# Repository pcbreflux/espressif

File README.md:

# espressif
espressif stuff (i.e. ESP32, ESP8266)

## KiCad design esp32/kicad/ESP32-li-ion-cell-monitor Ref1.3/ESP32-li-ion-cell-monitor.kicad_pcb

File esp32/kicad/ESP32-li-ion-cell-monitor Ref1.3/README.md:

# ESP32 Li-Ion Cell Monitor (:battery: i.e. 18650 ...  :zap:)
===========================

## Application: kicad

## Version: 5.0.0-fee4fd1~66~ubuntu18.04.1, release build

## Libraries:

    wxWidgets 3.0.4

    libcurl/7.58.0 OpenSSL/1.1.0g zlib/1.2.11 libidn2/2.0.4 libpsl/0.19.1 (+libidn2/2.0.4) nghttp2/1.30.0 librtmp/2.3

## Platform: Linux 4.15.0-29-generic x86_64, 64 bit, Little endian, wxGTK

## Build Info:

    wxWidgets: 3.0.4 (wchar_t,wx containers,compatible with 2.8) GTK+ 2.24

    Boost: 1.65.1

    OpenCASCADE Community Edition: 6.9.1

    Curl: 7.58.0

    Compiler: GCC 7.3.0 with C++ ABI 1011

## Build settings:

    USE_WX_GRAPHICS_CONTEXT=OFF

    USE_WX_OVERLAY=OFF

    KICAD_SCRIPTING=ON

    KICAD_SCRIPTING_MODULES=ON

    KICAD_SCRIPTING_WXPYTHON=OFF

    KICAD_SCRIPTING_ACTION_MENU=ON

    BUILD_GITHUB_PLUGIN=ON

    KICAD_USE_OCE=ON

    KICAD_USE_OCC=OFF

    KICAD_SPICE=ON

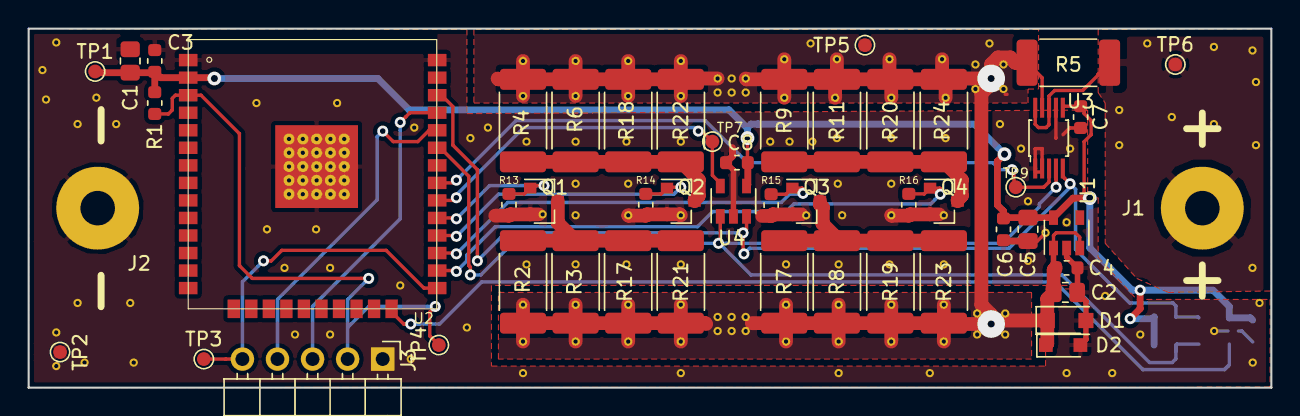
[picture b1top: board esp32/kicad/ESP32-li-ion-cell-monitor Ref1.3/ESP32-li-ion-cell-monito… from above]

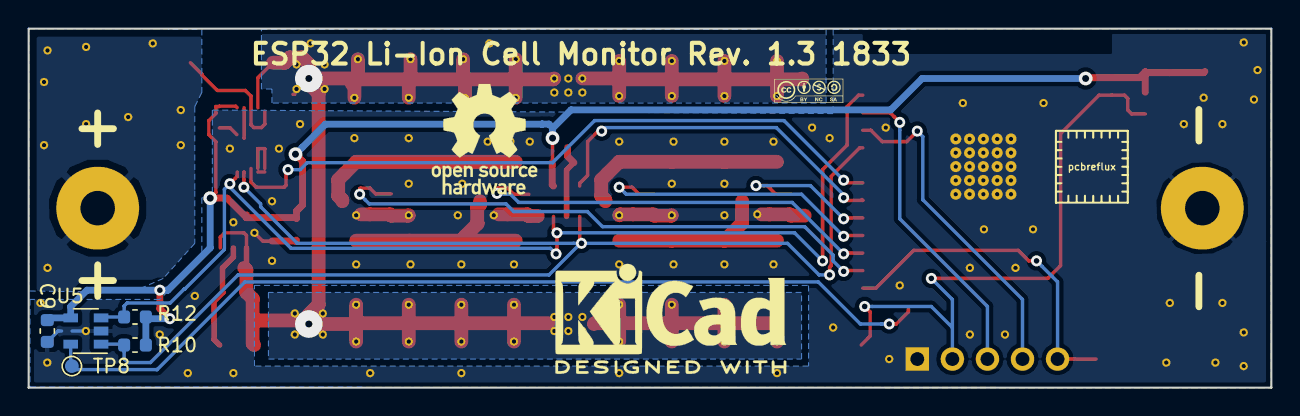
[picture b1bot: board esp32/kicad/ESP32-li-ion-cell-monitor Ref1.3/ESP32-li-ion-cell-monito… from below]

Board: 2 copper layers, 90.0 x 26.0 mm, 56 parts (5 on the bottom side), 21 nets.

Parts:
C1: 1u; C_0805_2012Metric
C2, C5: 10u; C_0805_2012Metric
C3, C4, C6, C7, C8, C9: 100n; C_0603_1608Metric
D1: MMSZ5V6CF; D_SOD-123F
D2: ESDZL5-1F4; D_SOD-323_HandSoldering
J1, J2: Conn_01x01_Female; SolderWirePad_1x01_Drill2.5mm
J3: Conn_01x05_Male; PinHeader_1x05_P2.54mm_Horizontal
Q1, Q2, Q3, Q4: Q_NMOS_GSD; SOT-23
R1, R10, R12: 10k; R_0603_1608Metric
R2, R3, R4, R6, R7, R8, R9, R11, R17, R18, R19, R20, R21, R22, R23, R24: 100R; R_2512_6332Metric_Pad1.52x3.35mm_HandSolder
R5: 100mR; R_2512_6332Metric_Pad1.52x3.35mm_HandSolder
R13, R14, R15, R16: 100k; R_0603_1608Metric
TP1, TP2, TP3, TP4, TP5, TP6, TP7, TP8, TP9: Test_Point; TestPoint_Pad_D1.0mm
U1: XC6220B281MR-G; SOT-23-5
U2: ESP-WROOM-32; ESP-WROOM-32-short
U3: INA226_SOT25-5; VSSOP-10_3.1x3.1mm_P0.5mm
U4: Si7060-00; SOT-23-5
U5: Si7060-01; SOT-23-5

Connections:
+2V8: C1.2, C3.2, C5.1, C6.1, C7.1, C8.2, C9.2, R1.2, R10.2, R12.2, TP1.1, U1.5, U2.2, U3.6, U4.4, U5.4
+BATT: J1.1, R5.2, TP6.1, U3.8, U3.10
/Alert1: TP9.1, U2.31, U3.3
/Alert2: TP7.1, U2.30, U4.5
/Alert3: TP8.1, U2.24, U5.5
/BOOT: J3.5, TP3.1, U2.25
/EN: J3.2, R1.1, TP4.1, U2.3
/RX: J3.4, U2.34
/SCL: R12.1, U2.36, U3.5, U4.3, U5.3
/SDA: R10.1, U2.33, U3.4, U4.1, U5.1
/TX: J3.3, U2.35
GND: C1.1, C2.2, C3.1, C4.2, C5.2, C6.2, C7.2, C8.1, C9.1, D1.2, D2.2, J2.1, J3.1, Q1.2, Q2.2, Q3.2, Q4.2, R13.1, R14.1, R15.1, R16.1, TP2.1, U1.2, U2.1, U2.38, U2.39, U3.1, U3.2, U3.7, U4.2, U5.2
unnamed: Q1.1, R13.2, U2.29
unnamed: Q1.3, R2.2, R3.2, R17.2, R21.2
unnamed: Q2.1, R14.2, U2.28
unnamed: Q2.3, R4.2, R6.2, R18.2, R22.2
unnamed: Q3.1, R15.2, U2.27
unnamed: Q3.3, R7.2, R8.2, R19.2, R23.2
unnamed: Q4.1, R16.2, U2.26
unnamed: Q4.3, R9.2, R11.2, R20.2, R24.2
VCC: C2.1, C4.1, D1.1, D2.1, R2.1, R3.1, R4.1, R5.1, R6.1, R7.1, R8.1, R9.1, R11.1, R17.1, R18.1, R19.1, R20.1, R21.1, R22.1, R23.1, R24.1, TP5.1, U1.1, U1.3, U3.9

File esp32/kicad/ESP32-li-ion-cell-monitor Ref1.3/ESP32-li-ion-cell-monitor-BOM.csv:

"Id";"Designator";"Package";"Quantity";"Designation";"Supplier and ref";
1;"REF**,REF**,REF**,REF**,REF**,REF**,REF**,REF**,REF**,REF**,REF**,REF**,REF**,REF**,REF**,REF**,REF**,REF**,REF**,REF**,REF**,REF**,REF**,REF**,REF**,REF**,REF**,REF**,REF**,REF**,REF**,REF**,REF**,REF**,REF**,REF**,REF**,REF**,REF**,REF**,REF**,REF**,REF**,REF**,REF**,REF**,REF**,REF**,REF**,REF**,REF**,REF**,REF**,REF**,REF**,REF**,REF**,REF**,REF**,REF**,REF**,REF**,REF**,REF**,REF**,REF**,REF**,REF**,REF**,REF**,REF**,REF**,REF**,REF**,REF**,REF**,REF**,REF**,REF**,REF**,REF**,REF**,REF**,REF**,REF**,REF**,REF**,REF**,REF**,REF**,REF**,REF**,REF**,REF**,REF**,REF**,REF**,REF**,REF**,REF**,REF**,REF**,REF**,REF**,REF**,REF**,REF**,REF**,REF**,REF**,REF**,REF**,REF**,REF**,REF**,REF**,REF**,REF**,REF**,REF**,REF**,REF**,REF**,REF**,REF**,REF**,REF**,REF**,REF**,REF**,REF**,REF**,REF**,REF**,REF**,REF**,REF**,REF**";"Via-0.6mm";138;"Via-0.6mm";;;
2;"TP9,TP1,TP2,TP3,TP4,TP5,TP6,TP7,TP8";"TestPoint_Pad_D1.0mm";9;"Test_Point";;;
3;"J3";"PinHeader_1x05_P2.54mm_Horizontal";1;"Conn_01x05_Male";;;
4;"U2";"ESP-WROOM-32-short";1;"ESP-WROOM-32";;;
5;"U4";"SOT-23-5";1;"Si7060-00";;;
6;"C1";"C_0805_2012Metric";1;"1u";;;
7;"C4,C6,C3,C7,C8,C9";"C_0603_1608Metric";6;"100n";;;
8;"C5,C2";"C_0805_2012Metric";2;"10u";;;
9;"Q1,Q2,Q3,Q4";"SOT-23";4;"Q_NMOS_GSD";;;
10;"R1,R10,R12";"R_0603_1608Metric";3;"10k";;;
11;"U5";"SOT-23-5";1;"Si7060-01";;;
12;"REF**";"pcbreflux_logo";1;"pcbreflux_logo";;;
13;"REF**";"OSHW-Logo_7.5x8mm_SilkScreen";1;"OSHW-Logo_7.5x8mm_SilkScreen";;;
14;"REF**";"KiCad-Logo2_8mm_SilkScreen";1;"KiCad-Logo2_8mm_SilkScreen";;;
15;"G***";"Logo_silk_CC-BY-NC-SA_5x2mm";1;"LOGO";;;
16;"D1";"D_SOD-123F";1;"MMSZ5V6CF";;;
17;"D2";"D_SOD-323_HandSoldering";1;"ESDZL5-1F4";;;
18;"R2,R3,R4,R6,R7,R8,R9,R11,R17,R18,R19,R20,R21,R22,R23,R24";"R_2512_6332Metric_Pad1.52x3.35mm_HandSolder";16;"100R";;;
19;"R5";"R_2512_6332Metric_Pad1.52x3.35mm_HandSolder";1;"100mR";;;
20;"U1";"SOT-23-5";1;"XC6220B281MR-G";;;
21;"U3";"VSSOP-10_3.1x3.1mm_P0.5mm";1;"INA226_SOT25-5";;;
22;"R13,R14,R15,R16";"R_0603_1608Metric";4;"100k";;;
23;"J1,J2";"SolderWirePad_1x01_Drill2.5mm";2;"Conn_01x01_Female";;;

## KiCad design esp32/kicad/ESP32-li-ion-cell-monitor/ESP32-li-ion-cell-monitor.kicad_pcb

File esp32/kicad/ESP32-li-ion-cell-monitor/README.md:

# ESP32 Li-Ion Cell Monitor (:battery: i.e. 18650 ...  :zap:)
===========================

## Application: kicad

## Version: 6.0.0-rc1-unknown-7dfc4e3~65~ubuntu18.04.1, release build

## Libraries:

    wxWidgets 3.0.4

    libcurl/7.58.0 OpenSSL/1.1.0g zlib/1.2.11 libidn2/2.0.4 libpsl/0.19.1 (+libidn2/2.0.4) nghttp2/1.30.0 librtmp/2.3

## Platform: Linux 4.15.0-29-generic x86_64, 64 bit, Little endian, wxGTK

## Build Info:

    wxWidgets: 3.0.4 (wchar_t,wx containers,compatible with 2.8) GTK+ 2.24

    Boost: 1.65.1

    OpenCASCADE Community Edition: 6.9.1

    Curl: 7.58.0

    Compiler: GCC 7.3.0 with C++ ABI 1011

## Build settings:

    USE_WX_GRAPHICS_CONTEXT=OFF

    USE_WX_OVERLAY=OFF

    KICAD_SCRIPTING=ON

    KICAD_SCRIPTING_MODULES=ON

    KICAD_SCRIPTING_WXPYTHON=OFF

    KICAD_SCRIPTING_ACTION_MENU=ON

    BUILD_GITHUB_PLUGIN=ON

    KICAD_USE_OCE=ON

    KICAD_USE_OCC=OFF

    KICAD_SPICE=ON

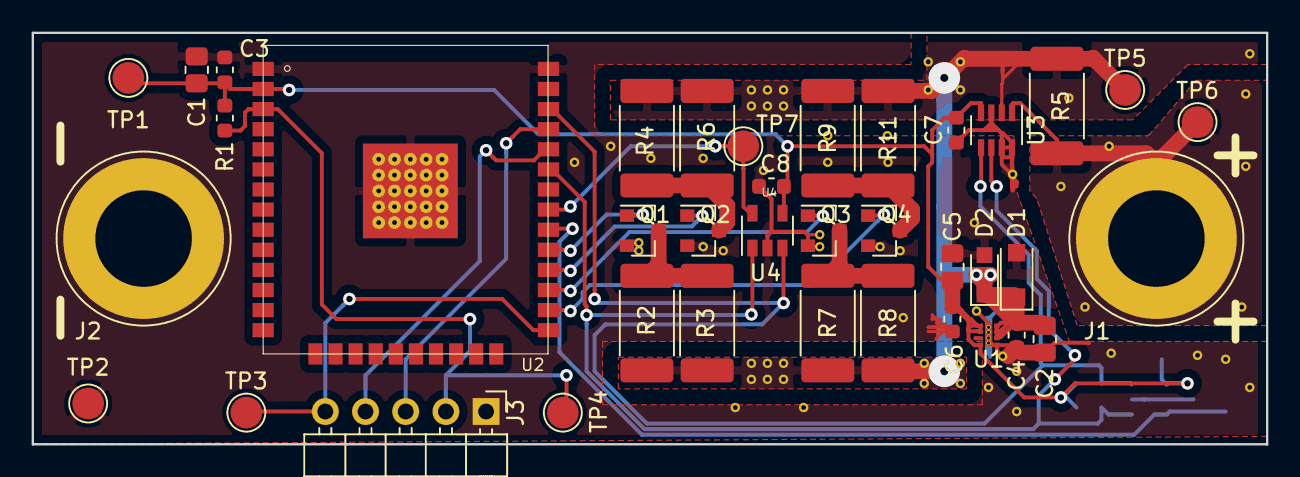
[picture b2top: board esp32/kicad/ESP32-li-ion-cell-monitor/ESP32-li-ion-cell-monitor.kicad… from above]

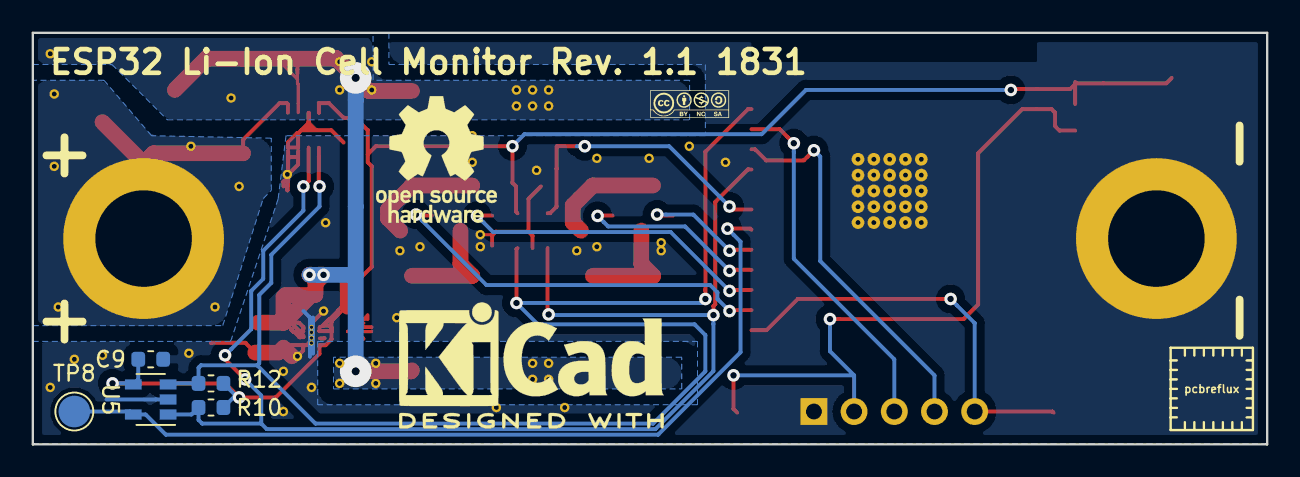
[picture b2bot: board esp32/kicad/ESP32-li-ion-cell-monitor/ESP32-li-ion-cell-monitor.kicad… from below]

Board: 2 copper layers, 78.0 x 26.0 mm, 43 parts (5 on the bottom side), 20 nets.

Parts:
C1, C2, C5: 1u; C_0805_2012Metric
C3, C4, C6, C7, C8, C9: 100n; C_0603_1608Metric
D1: MMSZ5V6CF; D_SOD-123F
D2: ESDZL5-1F4; D_SOD-323_HandSoldering
J1, J2: Conn_01x01_Female; Banana_Jack_1Pin
J3: Conn_01x05_Male; PinHeader_1x05_P2.54mm_Horizontal
Q1, Q2, Q3, Q4: Q_NMOS_GSD; SOT-23
R1, R10, R12: 10k; R_0603_1608Metric
R2, R3, R4, R6, R7, R8, R9, R11: 10R; R_2512_6332Metric_Pad1.52x3.35mm_HandSolder
R5: 100mR; R_2512_6332Metric_Pad1.52x3.35mm_HandSolder
TP1, TP2, TP3, TP4, TP5, TP6, TP7, TP8: Test_Point; TestPoint_Pad_D2.0mm
U1: NCP186B; XDFN8
U2: ES-WROOM-32; ESP-WROOM-32-short
U3: INA219_SOT23-8; SOT-23-8
U4: Si7060-00; SOT-23-5
U5: Si7060-01; SOT-23-5

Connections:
+3V: C1.2, C3.2, C5.1, C6.1, C7.2, C8.2, C9.2, R1.2, R10.2, R12.2, TP1.1, U1.1, U1.2, U1.4, U2.2, U3.4, U4.4, U5.4
+BATT: J1.1, R5.2, TP6.1, U3.1
/Alert1: TP7.1, U2.31, U4.5
/Alert2: TP8.1, U2.30, U5.5
/BOOT: J3.5, TP3.1, U2.25
/EN: J3.2, R1.1, TP4.1, U2.3
/RX: J3.4, U2.34
/SCL: R12.1, U2.36, U3.5, U4.3, U5.3
/SDA: R10.1, U2.33, U3.6, U4.1, U5.1
/TX: J3.3, U2.35
GND: C1.1, C2.2, C3.1, C4.2, C5.2, C6.2, C7.1, C8.1, C9.1, D1.2, D2.2, J2.1, J3.1, Q1.2, Q2.2, Q3.2, Q4.2, TP2.1, U1.5, U1.9, U2.1, U2.38, U2.39, U3.3, U3.7, U3.8, U4.2, U5.2
unnamed: Q1.1, U2.29
unnamed: Q1.3, R2.2, R3.2
unnamed: Q2.1, U2.28
unnamed: Q2.3, R4.2, R6.2
unnamed: Q3.1, U2.27
unnamed: Q3.3, R7.2, R8.2
unnamed: Q4.1, U2.26
unnamed: Q4.3, R9.2, R11.2
VCC: C2.1, C4.1, D1.1, D2.1, R2.1, R3.1, R4.1, R5.1, R6.1, R7.1, R8.1, R9.1, R11.1, TP5.1, U1.6, U1.7, U1.8, U3.2

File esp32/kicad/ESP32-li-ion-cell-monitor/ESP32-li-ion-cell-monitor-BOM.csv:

"Id";"Designator";"Package";"Quantity";"Designation";"Supplier and ref";
1;"U1";"XDFN8";1;"NCP186B";;;
2;"U3";"SOT-23-8";1;"INA219_SOT23-8";;;
3;"REF**,REF**,REF**,REF**,REF**,REF**,REF**,REF**,REF**,REF**,REF**,REF**,REF**,REF**,REF**,REF**,REF**,REF**,REF**,REF**,REF**,REF**,REF**,REF**,REF**,REF**,REF**,REF**,REF**,REF**,REF**,REF**,REF**,REF**,REF**,REF**,REF**,REF**,REF**,REF**,REF**,REF**,REF**,REF**,REF**,REF**,REF**,REF**,REF**,REF**,REF**,REF**,REF**,REF**,REF**,REF**,REF**,REF**";"Via-0.6mm";58;"Via-0.6mm";;;
4;"J3";"PinHeader_1x05_P2.54mm_Horizontal";1;"Conn_01x05_Male";;;
5;"U2";"ESP-WROOM-32-short";1;"ES-WROOM-32";;;
6;"U4";"SOT-23-5";1;"Si7060-00";;;
7;"C1,C5,C2";"C_0805_2012Metric";3;"1u";;;
8;"C4,C6,C3,C7,C8,C9";"C_0603_1608Metric";6;"100n";;;
9;"Q1,Q2,Q3,Q4";"SOT-23";4;"Q_NMOS_GSD";;;
10;"TP1,TP2,TP3,TP4,TP5,TP6,TP7,TP8";"TestPoint_Pad_D2.0mm";8;"Test_Point";;;
11;"R1,R10,R12";"R_0603_1608Metric";3;"10k";;;
12;"U5";"SOT-23-5";1;"Si7060-01";;;
13;"REF**";"pcbreflux_logo";1;"pcbreflux_logo";;;
14;"REF**";"OSHW-Logo_7.5x8mm_SilkScreen";1;"OSHW-Logo_7.5x8mm_SilkScreen";;;
15;"REF**";"KiCad-Logo2_8mm_SilkScreen";1;"KiCad-Logo2_8mm_SilkScreen";;;
16;"G***";"Logo_silk_CC-BY-NC-SA_5x2mm";1;"LOGO";;;
17;"D1";"D_SOD-123F";1;"MMSZ5V6CF";;;
18;"D2";"D_SOD-323_HandSoldering";1;"ESDZL5-1F4";;;
19;"R2,R3,R4,R6,R7,R8,R9,R11";"R_2512_6332Metric_Pad1.52x3.35mm_HandSolder";8;"10R";;;
20;"R5";"R_2512_6332Metric_Pad1.52x3.35mm_HandSolder";1;"100mR";;;
21;"J1,J2";"Banana_Jack_1Pin";2;"Conn_01x01_Female";;;

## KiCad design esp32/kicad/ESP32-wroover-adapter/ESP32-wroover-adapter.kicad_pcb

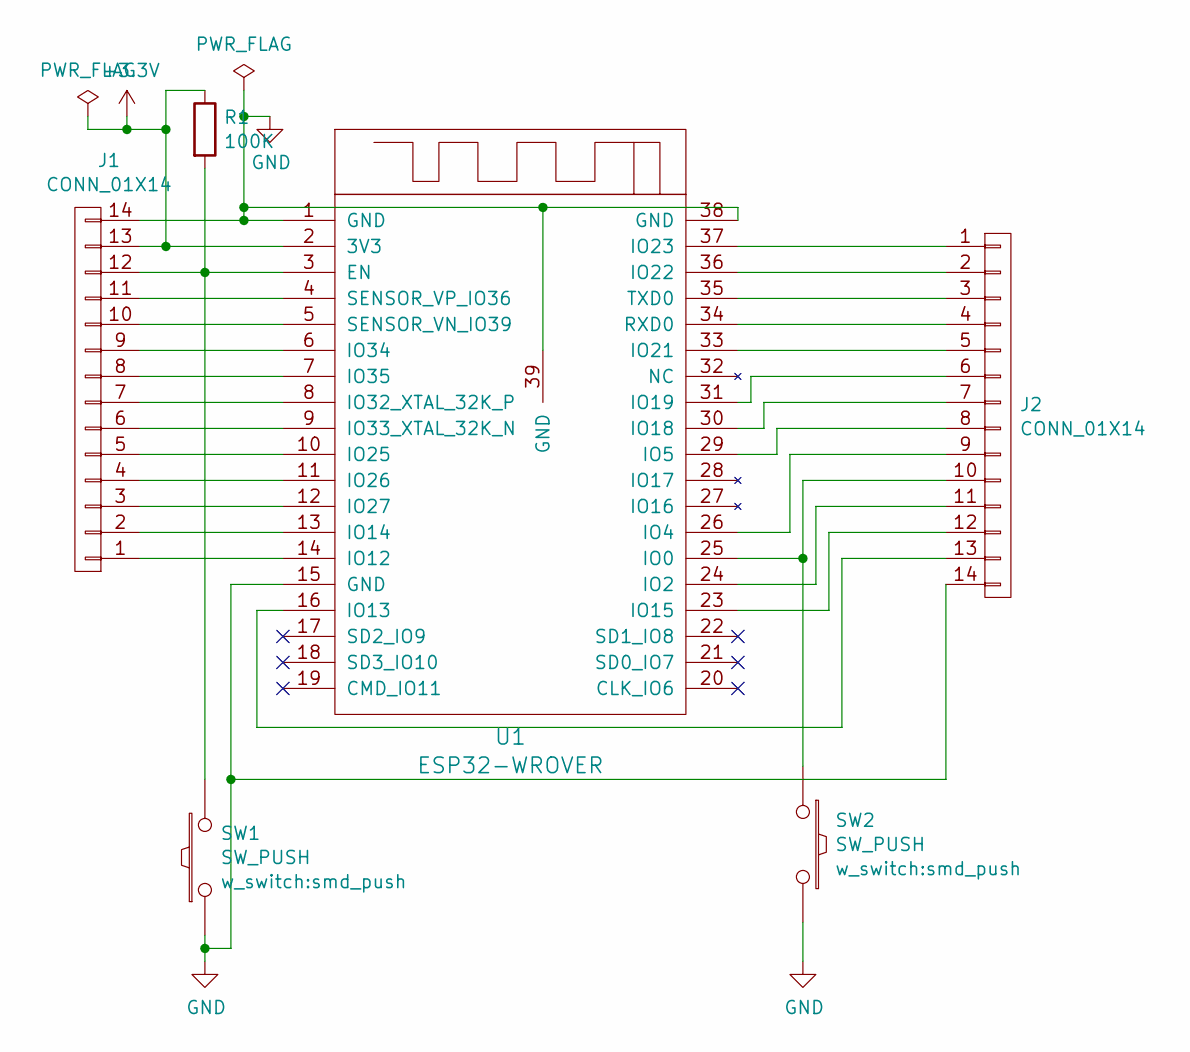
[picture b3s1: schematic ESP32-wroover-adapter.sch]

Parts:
J1, J2: CONN_01X14; Pin_Header_Straight_1x14_Pitch2.54mm
R1: 100K; r_0603
SW1, SW2: SW_PUSH; smd_push
U1: ESP32-WROVER; ESP32-WROVER-short

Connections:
+3V3: J1.13, R1.1, U1.2 (3V3)
GND: J1.14, J2.14, SW1.1, SW2.2, U1.1 (GND), U1.15 (GND), U1.38 (GND), U1.39 (GND)
unnamed: J1.1, U1.14 (IO12)
unnamed: J1.2, U1.13 (IO14)
unnamed: J1.3, U1.12 (IO27)
unnamed: J1.4, U1.11 (IO26)
unnamed: J1.5, U1.10 (IO25)
unnamed: J1.6, U1.9 (IO33_XTAL_32K_N)
unnamed: J1.7, U1.8 (IO32_XTAL_32K_P)
unnamed: J1.8, U1.7 (IO35)
unnamed: J1.9, U1.6 (IO34)
unnamed: J1.10, U1.5 (SENSOR_VN_IO39)
unnamed: J1.11, U1.4 (SENSOR_VP_IO36)
unnamed: J1.12, R1.2, SW1.2, U1.3 (EN)
unnamed: J2.1, U1.37 (IO23)
unnamed: J2.2, U1.36 (IO22)
unnamed: J2.3, U1.35 (TXD0)
unnamed: J2.4, U1.34 (RXD0)
unnamed: J2.5, U1.33 (IO21)
unnamed: J2.6, U1.31 (IO19)
unnamed: J2.7, U1.30 (IO18)
unnamed: J2.8, U1.29 (IO5)
unnamed: J2.9, U1.26 (IO4)
unnamed: J2.10, SW2.1, U1.25 (IO0)
unnamed: J2.11, U1.24 (IO2)
unnamed: J2.12, U1.23 (IO15)
unnamed: J2.13, U1.16 (IO13)

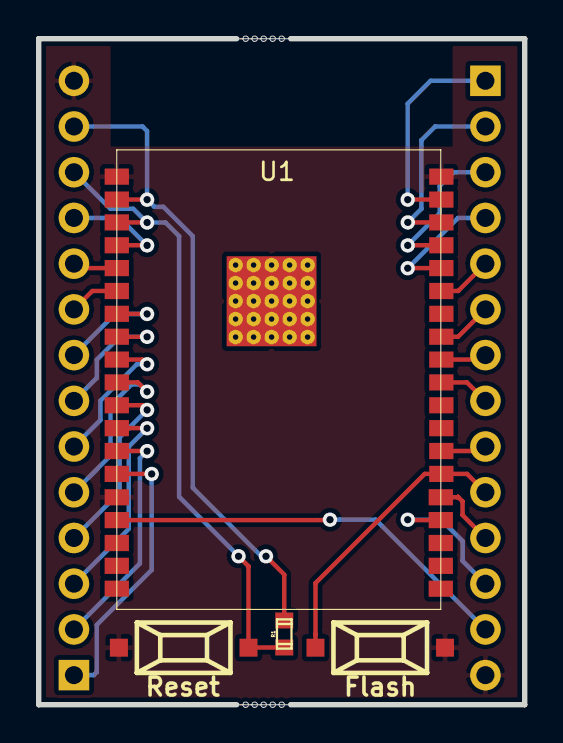
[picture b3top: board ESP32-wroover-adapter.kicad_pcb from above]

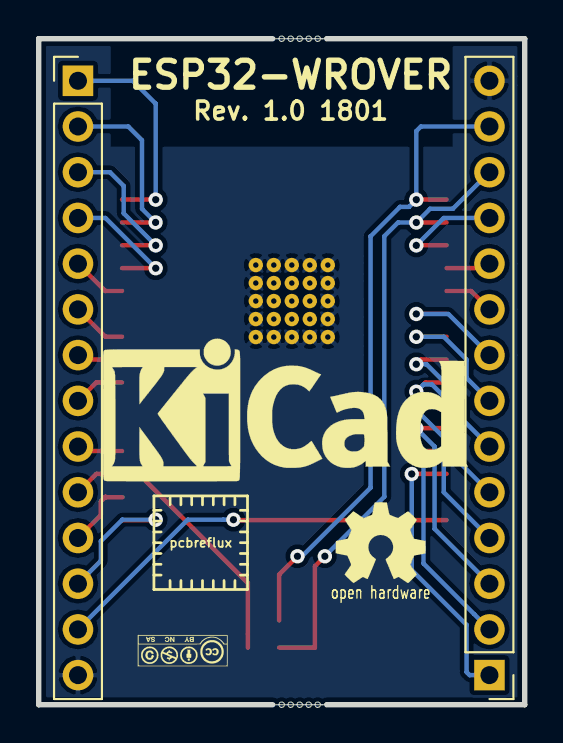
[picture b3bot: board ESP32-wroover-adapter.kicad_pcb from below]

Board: 2 copper layers, 27.0 x 37.0 mm, 6 parts (2 on the bottom side), 27 nets.

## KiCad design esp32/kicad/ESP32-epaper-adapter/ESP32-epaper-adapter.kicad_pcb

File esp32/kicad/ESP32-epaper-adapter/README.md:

ESP32 ePaper Adapter
===========================

This project uses information from this Project:

http://www.jsykora.info/2014/06/epd-display-working/

http://www.jsykora.info/welcome/

http://www.jsykora.info/2014/04/mailbag-epaper-display-module/

https://github.com/jsyk/PIP-Watch

see also https://github.com/jsyk/PIP-Watch/blob/master/License_Hardware.txt

Files using the KiCad development version!

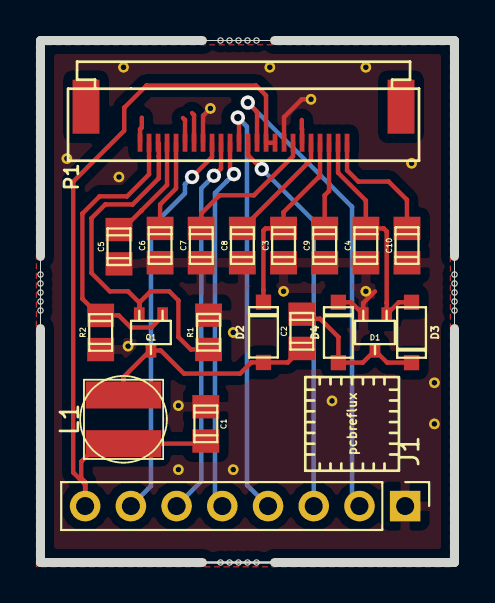
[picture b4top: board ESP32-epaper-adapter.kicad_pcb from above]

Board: 2 copper layers, 23.0 x 29.0 mm, 20 parts (0 on the bottom side), 20 nets.

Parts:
C1: 4u7/6V; c_0805
C2: 4u7/50V; c_0805
C3, C5, C6, C7, C8, C9, C10: 1u/50V; c_0805
C4: 2u2/50V; c_0805
D1: BAT30SWFILM; sot323
D2, D3, D4: MBR0530; sod123
J1: CONN_01X08; Pin_Header_Straight_1x08_Pitch2.54mm
L1: 68u; inductor_smd_4mmx4mm
P1: MOLEX_FPC_RCPT_24POS; MOLEX_FPC_RCPT_24POS_0_5MM
Q1: SI1308EDL; sot323
R1: 3R; r_0805
R2: 10k; r_0805

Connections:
/BUSY: J1.7, P1.9
/GDR: P1.2, Q1.1, R2.1
/PREVGH: C3.1, D2.1, P1.21
/PREVGL: C4.1, D1.1, D3.2, P1.23
/RESE: P1.3, Q1.3, R1.1
/SCLK: J1.3, P1.13
/SDA: J1.2, P1.14
/SW: C2.2, D2.2, L1.2, Q1.2
/VCCEPD: C1.1, J1.8, L1.1, P1.15, P1.16
/VCOM: C10.1, P1.24
/VDD: C7.1, P1.18
/VGH: C6.1, P1.5
/VGL: C5.1, P1.4
/VSH: C8.1, P1.20
/VSL: C9.1, P1.22
/nCS: J1.4, P1.12
/nDC: J1.5, P1.11
/nRES: J1.6, P1.10
GND: C1.2, C3.2, C4.2, C5.2, C6.2, C7.2, C8.2, C9.2, C10.2, D1.3, D4.1, J1.1, P1.8, P1.17, R1.2, R2.2
unnamed: C2.1, D1.2, D3.1, D4.2

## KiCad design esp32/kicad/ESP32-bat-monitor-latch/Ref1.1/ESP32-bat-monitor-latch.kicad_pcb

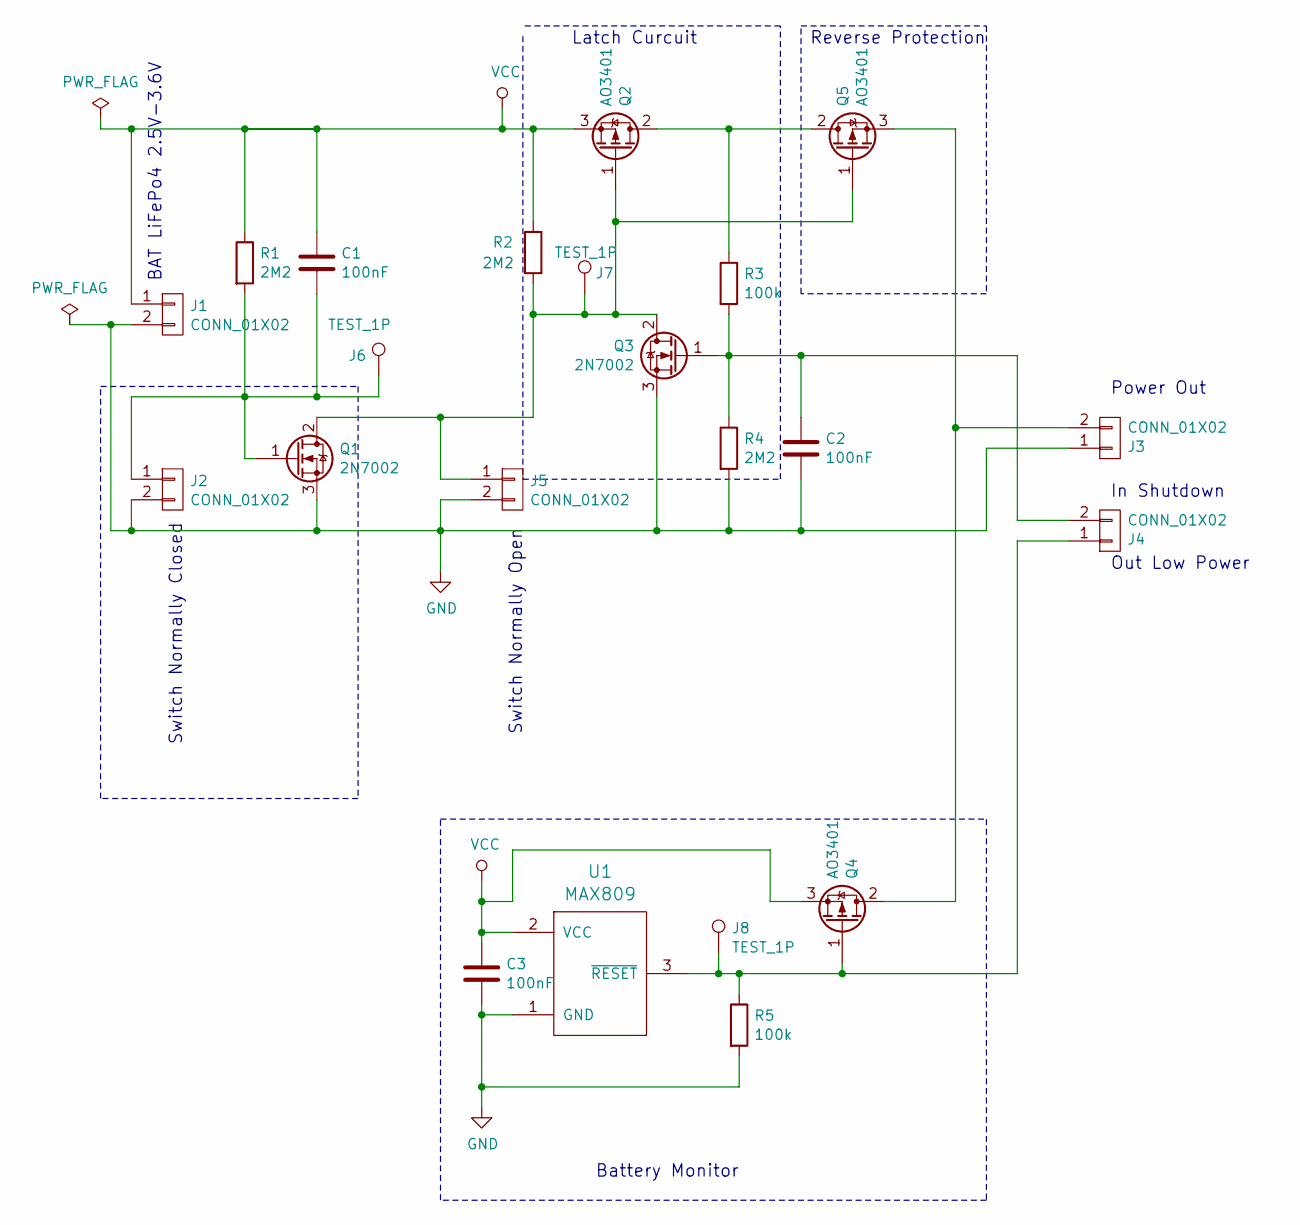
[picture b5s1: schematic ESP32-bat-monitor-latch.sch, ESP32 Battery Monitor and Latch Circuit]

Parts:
C1, C2, C3: 100nF; c_0603
J1, J2, J3, J4, J5: CONN_01X02; mkds_1,5-2
J6, J7, J8: TEST_1P; testpoint_1mm
Q1, Q3: 2N7002; sot23
Q2, Q4, Q5: AO3401; sot23
R1, R2, R4: 2M2; r_0603
R3, R5: 100k; r_0603
U1: MAX809; sot23

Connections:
GND: C2.2, C3.2, J1.2, J2.2, J3.1, J5.2, Q1.3 (S), Q3.3 (S), R4.2, R5.2, U1.1 (GND)
unnamed: C1.2, J2.1, J6.1, Q1.1 (G), R1.2
unnamed: C2.1, J4.2, Q3.1 (G), R3.2, R4.1
unnamed: J3.2, Q4.2 (D), Q5.3 (S)
unnamed: J4.1, J8.1, Q4.1 (G), R5.1, U1.3 (~RESET)
unnamed: J5.1, J7.1, Q1.2 (D), Q2.1 (G), Q3.2 (D), Q5.1 (G), R2.2
unnamed 6: Q2.2 (D), Q5.2 (D), R3.1; also elsewhere on the board
VCC: C1.1, C3.1, J1.1, Q2.3 (S), Q4.3 (S), R1.1, R2.1, U1.2 (VCC)

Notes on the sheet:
BAT LiFePo4 2.5V-3.6V
Switch Normally Closed
Power Out
In Shutdown
Out Low Power
Battery Monitor
Switch Normally Open
Latch Curcuit
Reverse Protection

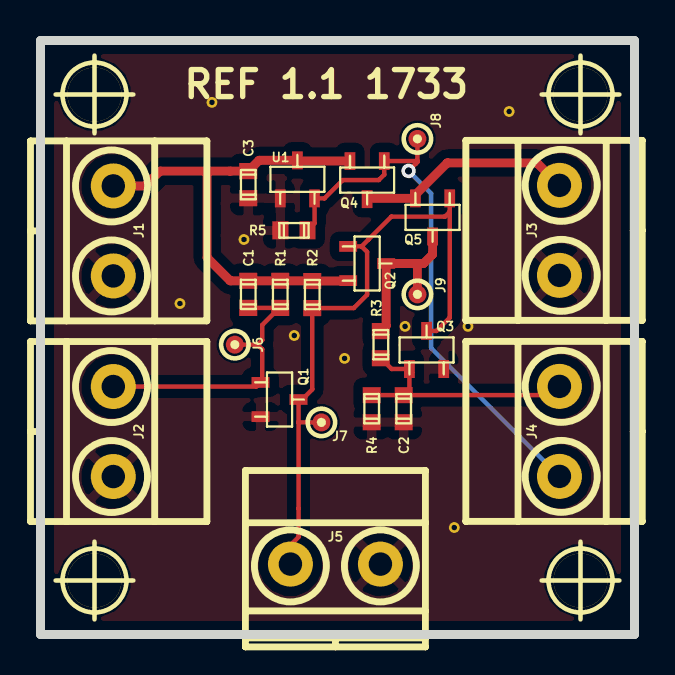
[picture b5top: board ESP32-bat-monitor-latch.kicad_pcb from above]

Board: 2 copper layers, 33.0 x 33.0 mm, 27 parts (0 on the bottom side), 8 nets.

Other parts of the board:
J9: TEST_1P; testpoint_1mm
hole_3mm, hole_3mm#2, hole_3mm#3, hole_3mm#4: VAL**; hole_3mm

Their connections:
unnamed 6: J9.1; also elsewhere on the board

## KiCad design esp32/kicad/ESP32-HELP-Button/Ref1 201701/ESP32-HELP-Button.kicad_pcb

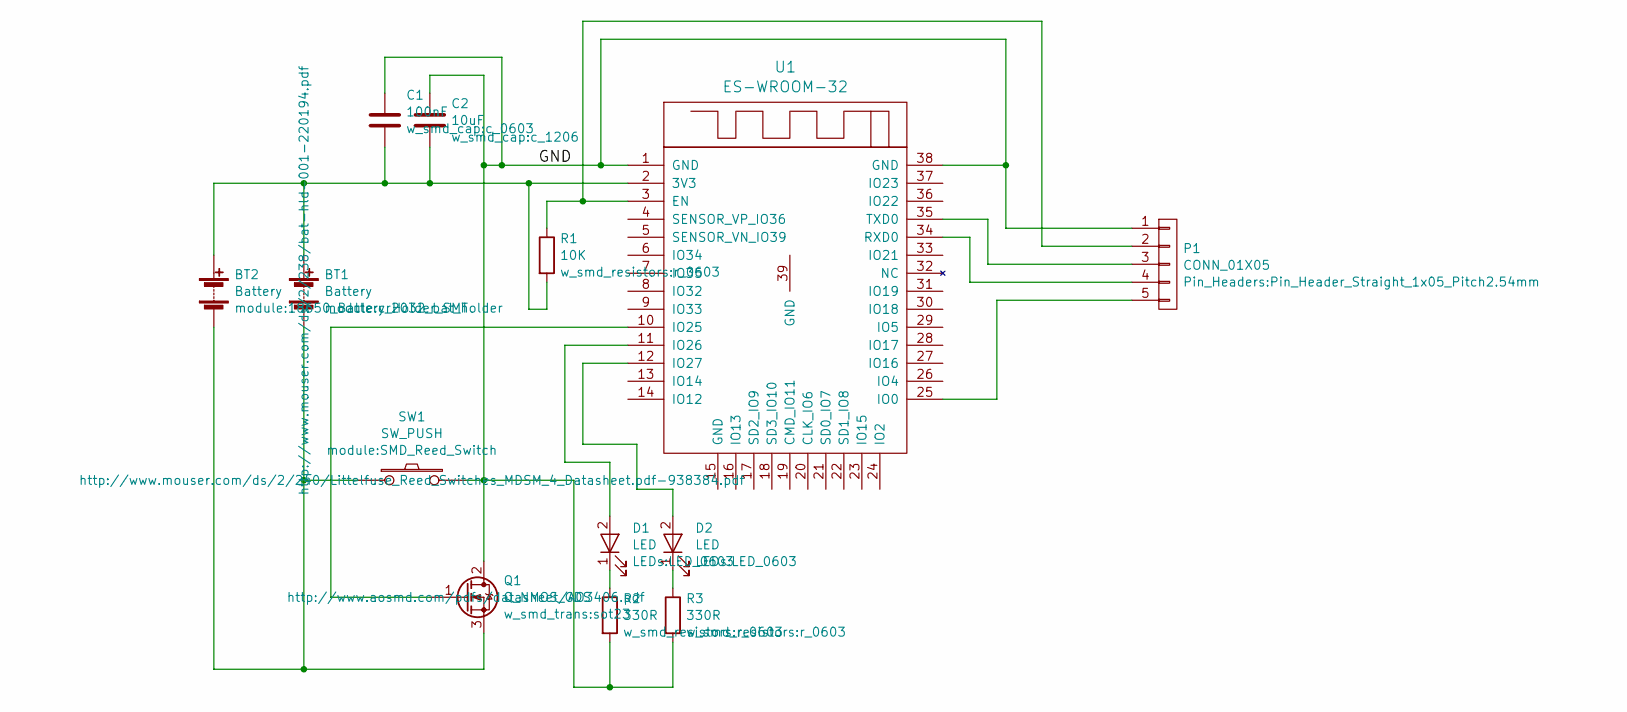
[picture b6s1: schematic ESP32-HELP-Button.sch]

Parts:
BT1: Battery; cr2032_bat_holder; MFG Part Num BAT-HLD-001
BT2: Battery; 18650_Battery_Holder_SMT; MFG Part Num 1042P
C1: 100nF; c_0603; MFG Part Num 100nF 0603 capacitor X7R
C2: 10uF; c_1206; MFG Part Num 10uF 1206 capacitor X7R
D1: LED; LED_0603; MFG Part Num led green 0603
D2: LED; LED_0603; MFG Part Num led red 0603
P1: CONN_01X05; Pin_Header_Straight_1x05_Pitch2.54mm; MFG Part Num 22-28-4012
Q1: Q_NMOS_GDS; sot23; MFG Part Num AO3406
R1: 10K; r_0603; MFG Part Num 10k 0603 resistor 10%
R2, R3: 330R; r_0603; MFG Part Num 330R 0603 resistor 10%
SW1: SW_PUSH; SMD_Reed_Switch; MFG Part Num MDSM-4R-7-13
U1: ES-WROOM-32; ESP-WROOM-32-short; MFG Part Num esp-wroom-32

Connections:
/GND: C1.1, C2.1, P1.1, Q1.2 (D), R2.2, R3.2, SW1.2, U1.1 (GND), U1.38 (GND)
unnamed: BT1.1 (+), BT2.1 (+), C1.2, C2.2, R1.2, U1.2 (3V3)
unnamed: BT1.2 (-), BT2.2 (-), Q1.3 (S), SW1.1
unnamed: D1.1 (K), R2.1
unnamed: D1.2 (A), U1.11 (IO26)
unnamed: D2.1 (K), R3.1
unnamed: D2.2 (A), U1.12 (IO27)
unnamed: P1.2, R1.1, U1.3 (EN)
unnamed: P1.3, U1.35 (TXD0)
unnamed: P1.4, U1.34 (RXD0)
unnamed: P1.5, U1.25 (IO0)
unnamed: Q1.1 (G), U1.10 (IO25)

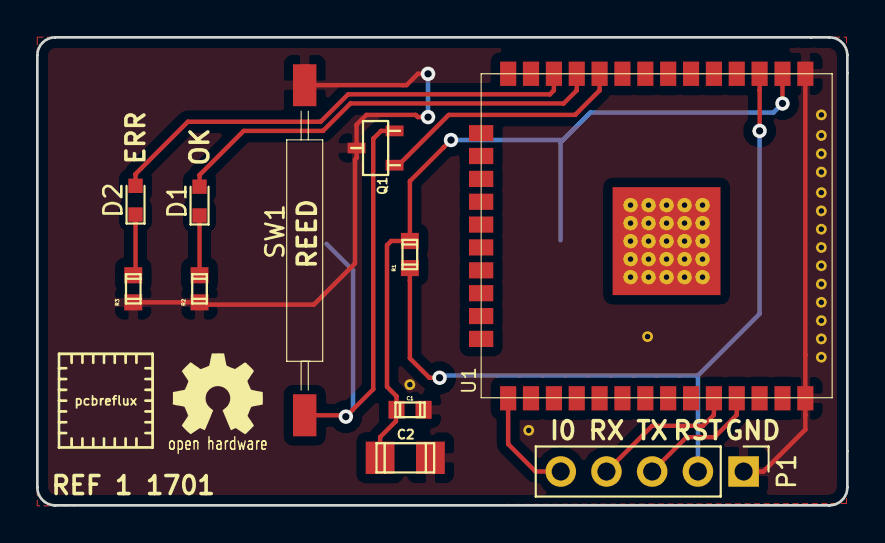
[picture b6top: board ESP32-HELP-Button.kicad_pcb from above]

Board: 2 copper layers, 45.0 x 26.0 mm, 12 parts (1 on the bottom side), 12 nets.

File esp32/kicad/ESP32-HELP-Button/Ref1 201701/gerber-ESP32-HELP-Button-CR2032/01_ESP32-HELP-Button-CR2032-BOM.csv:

Reference, Value, Footprint, Datasheet, MFG Name, MFG Part Num, 1st Distrib PN, 1st Distrib Link, 2nd Distrib PN, 2nd Distrib Link,,Val,Package,PosX,PosY,Rot,Side
U1,ES-WROOM-32,module:ESP-WROOM-32-short,http://espressif.com/sites/default/files/documentation/esp_w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,espressif,esp-wroom-32,ESP-32S,http://www.analoglamb.com/product/esp3212-wifi-bluetooth-com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,ESP-32S-ALB,http://www.analoglamb.com/product/esp-32s-alb/,,-,,,,,
P1,CONN_01X05,Pin_Headers:Pin_Header_Straight_1x05_Pitch2.54mm,http://www.molex.com/webdocs/datasheets/pdf/en-us//002228505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,Molex,22-28-4012,pin header 40 pin male 2.54mm,https://www.aliexpress.com/wholesale?SearchText=pin+header+4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,538-22-28-5051,http://www.mouser.de/ProductDetail/Molex/22-28-5051/?qs=sGAE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,,-,,,,,
BT1,Battery,module:cr2032_bat_holder,http://www.mouser.com/ds/2/238/bat-hld-001-220194.pdf,Linx Technologies,BAT-HLD-001,712-BAT-HLD-001,http://www.mouser.de/ProductDetail/Linx-Technologies/BAT-HLD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,BAT-HLD-001-THM-ND,http://www.digikey.com/product-detail/en/linx-technologies-i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,,Battery,cr2032_bat_holder,95.067961,-58.473131,0.000000,bottom
Q1,Q_NMOS_GDS,w_smd_trans:sot23,http://www.aosmd.com/pdfs/datasheet/AO3406.pdf,Alpha & Omega Semiconductor Inc.,AO3406,ao3406 100pcs,https://www.aliexpress.com/wholesale?SearchText=ao3406+100pcs,785-1005-1-ND,http://www.digikey.com/product-detail/en/alpha-omega-semicon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,,Q_NMOS_GDS,sot23,97.790000,-53.149500,90.000000,top
SW1,SW_PUSH,module:SMD_Reed_Switch,http://www.mouser.com/ds/2/240/Littelfuse_Reed_Switches_MDSM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,Hamlin / Littelfuse,MDSM-4R-7-13,934-MDSM-4R-7-13,http://www.mouser.de/ProductDetail/Hamlin-Littelfuse/MDSM-4R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,F7839CT-ND,http://www.digikey.com/product-detail/en/littelfuse-inc/MDSM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,,SW_PUSH,SMD_Reed_Switch,93.853000,-67.997000,90.000000,top
R1,10K,w_smd_resistors:r_0603,,arbitrary,10k 0603 resistor 10%,10k 0603 resistor 1% 1000pcs,https://www.aliexpress.com/wholesale?SearchText=10k+0603+res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,603-RC0603JR-0710KL,http://www.mouser.de/ProductDetail/Yageo/RC0603JR-0710KL/?qs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,,10K,r_0603,99.695000,-59.065160,270.000000,top
R2,330R,w_smd_resistors:r_0603,,arbitrary,330R 0603 resistor 10%,330R 0603 resistor 10% 1000pcs,https://www.aliexpress.com/wholesale?SearchText=330R+0603+re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,603-RC0603JR-07330RL,http://www.mouser.de/ProductDetail/Yageo/RC0603JR-07330RL/?q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,,330R,r_0603,88.011000,-60.970160,90.000000,top
D1,LED,LEDs:LED_0603,,arbitrary,led green 0603,led green 0603 100pcs,https://www.aliexpress.com/wholesale?SearchText=led+green+06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,859-LTST-C190GKT,http://www.mouser.de/ProductDetail/Lite-On/LTST-C190GKT/?qs=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,,LED,LED_0603,88.011000,-56.096000,90.000000,top
D2,LED,LEDs:LED_0603,,arbitrary,led red 0603,led red 0603 100pcs,https://www.aliexpress.com/wholesale?SearchText=led+red+0603+100pcs,859-LTST-C190KRKT,http://www.mouser.de/ProductDetail/Lite-On/LTST-C190KRKT/?qs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,,LED,LED_0603,84.455000,-56.045000,90.000000,top
C2,10uF,w_smd_cap:c_1206,,arbitrary,10uF 1206 capacitor X7R,10uF 1206 capacitor X7R 100pcs,https://www.aliexpress.com/wholesale?SearchText=10uF+1206+ca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,581-1206ZC106KAT2A,http://www.mouser.de/ProductDetail/AVX/1206ZC106KAT2A/?qs=sG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,,10uF,c_1206,99.441000,-70.358000,0.000000,top
C1,100nF,w_smd_cap:c_0603,,arbitrary,100nF 0603 capacitor X7R,100nF 0603 capacitor X7R 1000pcs,https://www.aliexpress.com/wholesale?SearchText=100nF+0603+c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,710-885012206020,http://www.mouser.de/ProductDetail/Wurth-Electronics/8850122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,,100nF,c_0603,99.705160,-67.691000,0.000000,top
BT2,Battery,module:18650_Battery_Holder_SMT,http://www.mouser.com/ds/2/215/042P-744096.pdf,Keystone Electronics,1042P,18650 Battery Holder Battery Storage Box With Bronze PinsTBH-18650-1C-SMT,https://www.aliexpress.com/item/5Pcs-lot-18650-Battery-Holde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,534-1042P,http://www.mouser.de/ProductDetail/Keystone-Electronics/1042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,,-,,,,,
R3,330R,w_smd_resistors:r_0603,,arbitrary,330R 0603 resistor 10%,330R 0603 resistor 10% 1000pcs,https://www.aliexpress.com/wholesale?SearchText=330R+0603+re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,603-RC0603JR-07330RL,http://www.mouser.de/ProductDetail/Yageo/RC0603JR-07330RL/?q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,,330R,r_0603,84.328000,-60.970160,90.000000,top

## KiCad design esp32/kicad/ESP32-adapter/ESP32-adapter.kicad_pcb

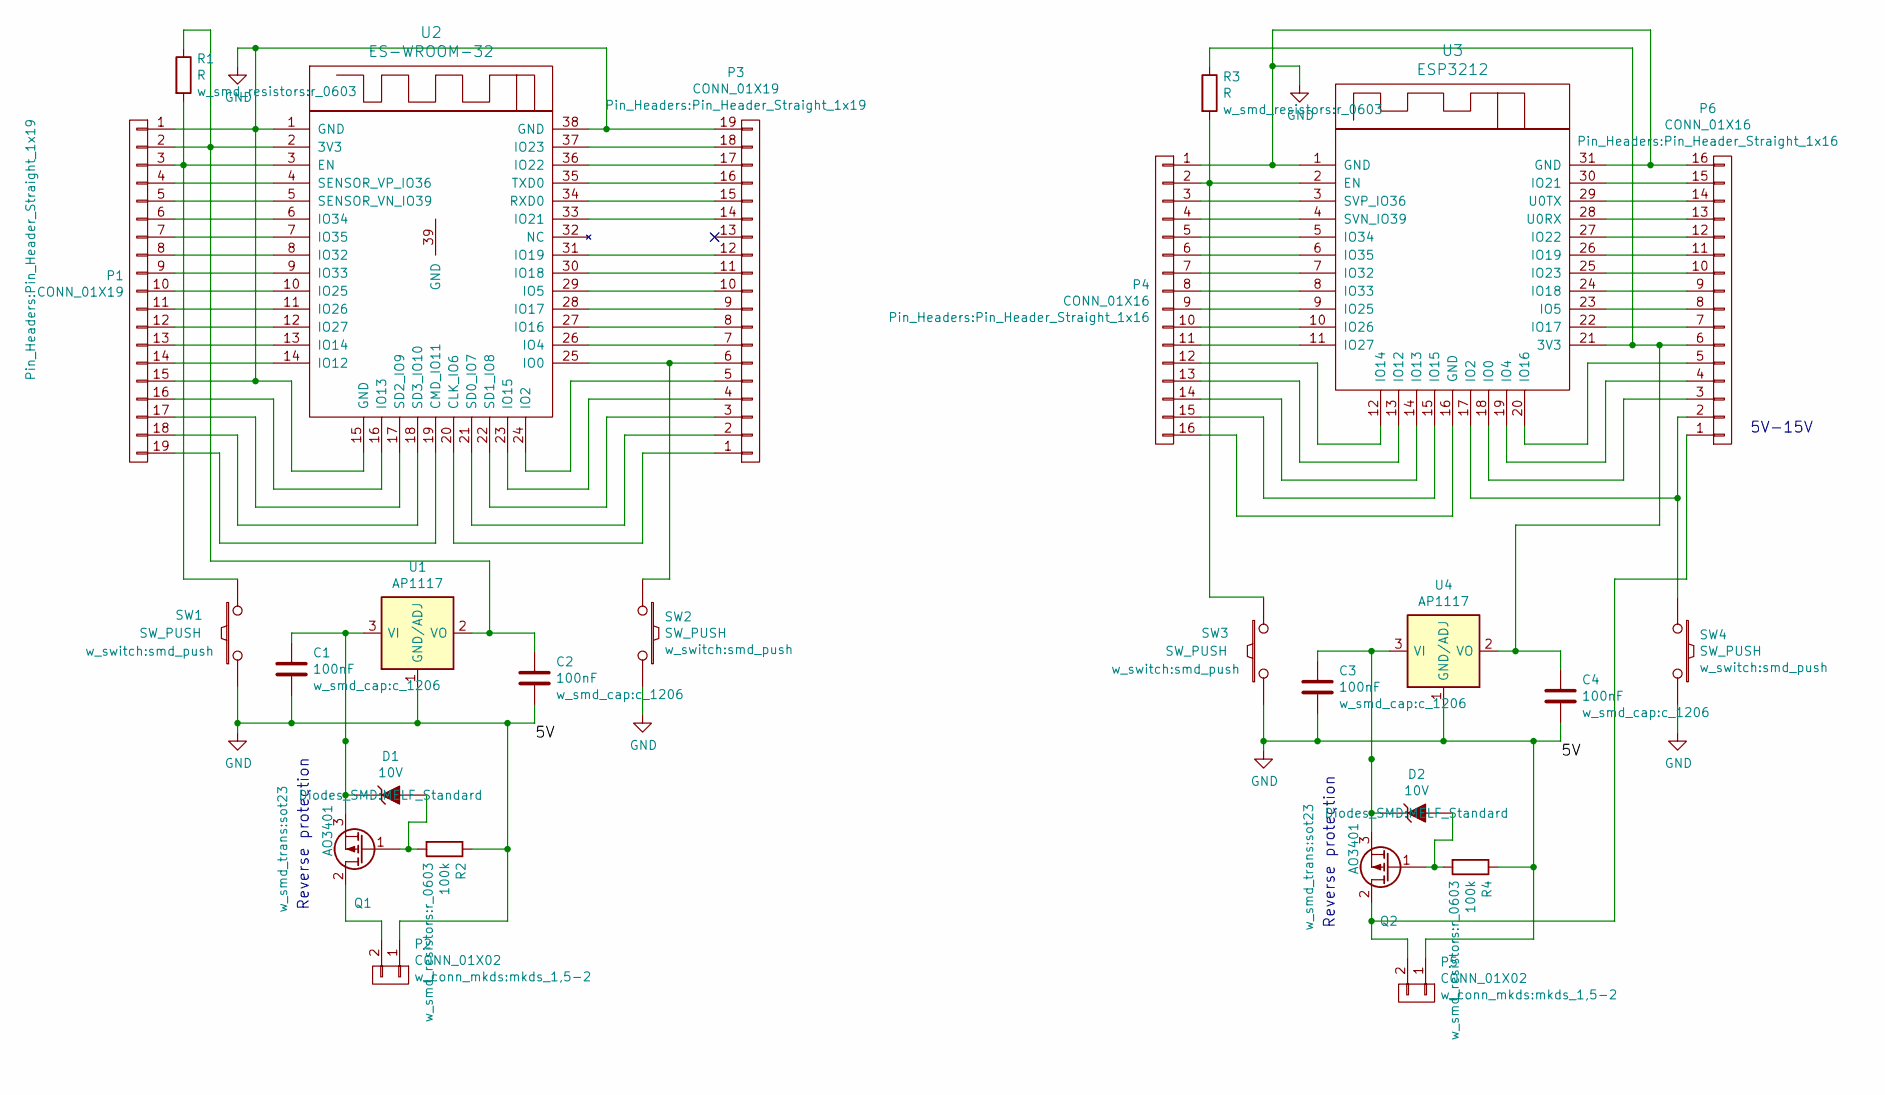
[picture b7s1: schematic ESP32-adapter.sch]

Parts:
C1, C2, C3, C4: 100nF; c_1206
D1, D2: 10V; MELF_Standard
P1, P3: CONN_01X19; Pin_Header_Straight_1x19
P2, P5: CONN_01X02; mkds_1,5-2
P4, P6: CONN_01X16; Pin_Header_Straight_1x16
Q1, Q2: AO3401; sot23
R1, R3: R; r_0603
R2, R4: 100k; r_0603
SW1, SW2, SW3, SW4: SW_PUSH; smd_push
U1, U4: AP1117; SOT-223
U2: ES-WROOM-32; ESP-WROOM-32
U3: ESP3212

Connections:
GND: C1.2, C2.2, C3.2, C4.2, P1.1, P1.15, P2.1, P3.19, P4.1, P5.1, P6.16, R2.1, R4.1, SW1.1, SW2.2, SW3.1, SW4.2, U1.1 (GND/ADJ), U2.1 (GND), U2.15 (GND), U2.38 (GND), U3.1 (GND), U3.31 (GND), U4.1 (GND/ADJ)
unnamed: C1.1, D1.1 (K), Q1.3 (S), U1.3 (VI)
unnamed: C2.1, P1.2, R1.1, U1.2 (VO), U1.4 (VO), U2.2 (3V3)
unnamed: C3.1, D2.1 (K), Q2.3 (S), U4.3 (VI)
unnamed: C4.1, P6.6, R3.1, U3.21 (3V3), U4.2 (VO), U4.4 (VO)
unnamed: D1.2 (A), Q1.1 (G), R2.2
unnamed: D2.2 (A), Q2.1 (G), R4.2
unnamed: P1.3, R1.2, SW1.2, U2.3 (EN)
unnamed: P1.4, U2.4 (SENSOR_VP_IO36)
unnamed: P1.5, U2.5 (SENSOR_VN_IO39)
unnamed: P1.6, U2.6 (IO34)
unnamed: P1.7, U2.7 (IO35)
unnamed: P1.8, U2.8 (IO32)
unnamed: P1.9, U2.9 (IO33)
unnamed: P1.10, U2.10 (IO25)
unnamed: P1.11, U2.11 (IO26)
unnamed: P1.12, U2.12 (IO27)
unnamed: P1.13, U2.13 (IO14)
unnamed: P1.14, U2.14 (IO12)
unnamed: P1.16, U2.16 (IO13)
unnamed: P1.17, U2.17 (SD2_IO9)
unnamed: P1.18, U2.18 (SD3_IO10)
unnamed: P1.19, U2.19 (CMD_IO11)
unnamed: P2.2, Q1.2 (D)
unnamed: P3.1, U2.20 (CLK_IO6)
unnamed: P3.2, U2.21 (SD0_IO7)
unnamed: P3.3, U2.22 (SD1_IO8)
unnamed: P3.4, U2.23 (IO15)
unnamed: P3.5, U2.24 (IO2)
unnamed: P3.6, SW2.1, U2.25 (IO0)
unnamed: P3.7, U2.26 (IO4)
unnamed: P3.8, U2.27 (IO16)
unnamed: P3.9, U2.28 (IO17)
unnamed: P3.10, U2.29 (IO5)
unnamed: P3.11, U2.30 (IO18)
unnamed: P3.12, U2.31 (IO19)
unnamed: P3.14, U2.33 (IO21)
unnamed: P3.15, U2.34 (RXD0)
unnamed: P3.16, U2.35 (TXD0)
unnamed: P3.17, U2.36 (IO22)
unnamed: P3.18, U2.37 (IO23)
unnamed: P4.2, R3.2, SW3.2, U3.2 (EN)
unnamed: P4.3, U3.3 (SVP_IO36)
unnamed: P4.4, U3.4 (SVN_IO39)
unnamed: P4.5, U3.5 (IO34)
unnamed: P4.6, U3.6 (IO35)
unnamed: P4.7, U3.7 (IO32)
unnamed: P4.8, U3.8 (IO33)
unnamed: P4.9, U3.9 (IO25)
unnamed: P4.10, U3.10 (IO26)
unnamed: P4.11, U3.11 (IO27)
unnamed: P4.12, U3.12 (IO14)
unnamed: P4.13, U3.13 (IO12)
unnamed: P4.14, U3.14 (IO13)
unnamed: P4.15, U3.15 (IO15)
unnamed: P4.16, U3.16 (GND)
unnamed: P5.2, P6.1, Q2.2 (D)
unnamed: P6.2, SW4.1, U3.17 (IO2)
unnamed: P6.3, U3.18 (IO0)
unnamed: P6.4, U3.19 (IO4)
unnamed: P6.5, U3.20 (IO16)
unnamed: P6.7, U3.22 (IO17)
unnamed: P6.8, U3.23 (IO5)
unnamed: P6.9, U3.24 (IO18)
unnamed: P6.10, U3.25 (IO23)
unnamed: P6.11, U3.26 (IO19)
unnamed: P6.12, U3.27 (IO22)
unnamed: P6.13, U3.28 (U0RX)
unnamed: P6.14, U3.29 (U0TX)
unnamed: P6.15, U3.30 (IO21)

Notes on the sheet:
Reverse protection
5V-15V
